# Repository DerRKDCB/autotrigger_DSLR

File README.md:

# autotrigger_DSLR
Device to automaticly take a number of long exposure pictures designed for astrophotography. 
Works with any DSLR that has a 2.5mm jack remote trigger connector and a bulb exposure mode. Here is a [Video](https://www.youtube.com/watch?v=2kZ-wBnaWUU "Video") with the device in Action

## How to use
The device uses a 2.5mm headphoe jack to simulate an remote trigger. It is powered my USB. Uses SSD1306 OLED Display as Display. With 4 buttons you can change the exposure time and the number of Pictures to take. The controller is an ESP8266 (ESP-12F module), so wifi capabilities could be implemented (**but are not, yet**).

1. Plug the USB into any USB Power source (Powerbank/Phone Charger/...) to power the device. Power consumtion is only 50mA so any Power source should work. Make sure you have a Power source that doesn't switch off because not enough current is detected.
2. Plug the headphone jack into the external/remote trigger socket of the camera.
3. Turn on the camera and change the settings to bulb mode for long exposures, if you want short exposures (under 1s) adjust exposure time at the camera accordingly.
4. Change exposure time on the autotrigger with the UP and DOWN buttons. (1s - 300s, range can be changed in code)
5. Press NEXT to select number of Exposures.
6. Change number of exposures to how much exposures you want UP and DOWN buttons. (1 - 100, range can be changed in code)
7. Press START to start the configured Series of Exposures.
8. While one Session is runnig, some info is displayed (exposure number, time of current exposure, total time)
9. Wait until session is finished or press NEXT to abort an session (current exposue will be finished)

## Building

### Ordering PCB and Parts

Order the PCB from a manufacturer you like, i use [JLCPCB](https://jlcpcb.com/ "JLCPCB"), by uploading the [prepared gerber files](KiCAD/autotrigger_dslr_v1.zip).

#### Partslist:
| Part  | Value  | Package  | Comment  | Link  |
| ------------ | ------------ | ------------ | ------------ | ------------ |
| C1  | 10uF  | 0805  |   | https://www.lcsc.com/product-detail/Multilayer-Ceramic-Capacitors-MLCC-SMD-SMT_FH-Guangdong-Fenghua-Advanced-Tech-0805X106M160NT_C2832123.html  |
| C2  | 10uF  | 0805  |   | https://www.lcsc.com/product-detail/Multilayer-Ceramic-Capacitors-MLCC-SMD-SMT_FH-Guangdong-Fenghua-Advanced-Tech-0805X106M160NT_C2832123.html  |
| C3  | 100nF  | 0805  |   | https://www.lcsc.com/product-detail/Multilayer-Ceramic-Capacitors-MLCC-SMD-SMT_FH-BK-Guangdong-Fenghua-Bangke-Elec-0805B104J500NT_C2830722.html  |
| C4  | 10uF  | 0805  |   | https://www.lcsc.com/product-detail/Multilayer-Ceramic-Capacitors-MLCC-SMD-SMT_FH-Guangdong-Fenghua-Advanced-Tech-0805X106M160NT_C2832123.html  |
| C5  | 100nF  | 0805  |   | https://www.lcsc.com/product-detail/Multilayer-Ceramic-Capacitors-MLCC-SMD-SMT_FH-BK-Guangdong-Fenghua-Bangke-Elec-0805B104J500NT_C2830722.html  |
| D1  | 1N5819  | SOD-123  |   | https://www.lcsc.com/product-detail/Schottky-Barrier-Diodes-SBD_ZHIDE-1N5819W_C2683619.html  |
| D2  | 1N5819  | SOD-123   |   | https://www.lcsc.com/product-detail/Schottky-Barrier-Diodes-SBD_ZHIDE-1N5819W_C2683619.html  |
| F1  | 500mA  | 1812  | Polyfuse  | https://www.lcsc.com/product-detail/Resettable-Fuses_TECHFUSE-mSMD050-15V_C70110.html  |
| J1  |   | 5x2.54mm  | Pin Header Female  | https://www.lcsc.com/product-detail/Female-Headers_Ckmtw-Shenzhen-Cankemeng-B-2200S05P-A120_C124414.html  |
| J2  | SSD1306  | SSD1306  | Display, look for pinout *GND VCC SCL SDA* , 4Pin, White | https://www.aliexpress.com/item/32638662748.html |
| K1  | G6K  | G6K-2F  | Omron Relay  | https://www.lcsc.com/product-detail/Signal-Relays_Omron-Electronics-G6K-2F-Y-TR-DC5_C47190.html  |
| Q1  | MosFET  | SOT-23  | N-Channel  | https://www.lcsc.com/product-detail/MOSFETs_Sinopower-Semicon-SM2326NSANC-TRG_C368561.html  |
| R1  | 10k  | 0805  |   | https://www.lcsc.com/product-detail/Chip-Resistor-Surface-Mount_TyoHM-RMC080510K1-N_C269742.html  |
| R2  | 10k  | 0805  |   | https://www.lcsc.com/product-detail/Chip-Resistor-Surface-Mount_TyoHM-RMC080510K1-N_C269742.html  |
| R3  | 1k  | 0805  |   | https://www.lcsc.com/product-detail/Chip-Resistor-Surface-Mount_TyoHM-RMC08051K5-N_C269727.html  |
| R4  | 10k  | 0805  |   | https://www.lcsc.com/product-detail/Chip-Resistor-Surface-Mount_TyoHM-RMC080510K1-N_C269742.html  |
| R5  | 5k  | 0805  |   | https://www.lcsc.com/product-detail/Chip-Resistor-Surface-Mount_Viking-Tech-ARG05DTC5001_C2828783.html  |
| R6  | 5k  | 0805  |   | https://www.lcsc.com/product-detail/Chip-Resistor-Surface-Mount_Viking-Tech-ARG05DTC5001_C2828783.html  |
| R7  | 5k  | 0805  |   | https://www.lcsc.com/product-detail/Chip-Resistor-Surface-Mount_Viking-Tech-ARG05DTC5001_C2828783.html  |
| R8  | 5k  | 0805  |   | https://www.lcsc.com/product-detail/Chip-Resistor-Surface-Mount_Viking-Tech-ARG05DTC5001_C2828783.html  |
| R9  | 1k  | 0805  |   | https://www.lcsc.com/product-detail/Chip-Resistor-Surface-Mount_TyoHM-RMC08051K5-N_C269727.html  |
| R10  | 10k  | 0805  |   | https://www.lcsc.com/product-detail/Chip-Resistor-Surface-Mount_TyoHM-RMC080510K1-N_C269742.html  |
| R11  | 1k  | 0805  |   | https://www.lcsc.com/product-detail/Chip-Resistor-Surface-Mount_TyoHM-RMC08051K5-N_C269727.html  |
| SW1  | pushbutton  | SPST SMD  |   | https://www.lcsc.com/product-detail/Tactile-Switches_XKB-Connectivity-TS-1101-C-W_C318938.html  |
| SW2  | pushbutton  | SPST SMD  |   | https://www.lcsc.com/product-detail/Tactile-Switches_XKB-Connectivity-TS-1101-C-W_C318938.html  |
| SW3  | pushbutton  | THT 6x6x10mm  |   | https://www.lcsc.com/product-detail/Tactile-Switches_G-Switch-GT-TC096A-H100-L1_C963363.html  |
| SW4  | pushbutton  | THT 6mm_H9.5mm  |   | https://www.lcsc.com/product-detail/Tactile-Switches_G-Switch-GT-TC096A-H100-L1_C963363.html  |
| SW5  | pushbutton  | THT 6mm_H9.5mm  |   | https://www.lcsc.com/product-detail/Tactile-Switches_G-Switch-GT-TC096A-H100-L1_C963363.html  |
| SW6  | pushbutton  | THT 6mm_H9.5mm  |   | https://www.lcsc.com/product-detail/Tactile-Switches_G-Switch-GT-TC096A-H100-L1_C963363.html  |
| U1  | ESP8266  | ESP-12F  |   | https://www.lcsc.com/product-detail/WiFi-Modules_Ai-Thinker-ESP-12F-ESP8266MOD_C82891.html  |
| U2  | AMS1117-3.3  | SOT-223-3  |   | https://www.lcsc.com/product-detail/Linear-Voltage-Regulators-LDO_PUOLOP-AMS1117-3-3_C351784.html  |

#### You also need:
- 1x USB A cable (any can be used because it's solderd directly to the pcb)
- 1x 2.5mm headphone jack cable https://www.aliexpress.com/item/4001182848617.html
- 8x M2.5 5mm bolts https://www.aliexpress.com/item/32963722509.html
- cable ties for strain relief
- tape (electrical/kepton/... doesn't really matter)
- For programming: USB to serial Adapter and jumper cables

### 3D Printing
Print [case](FreeCAD/3dp/stl/case-case.stl) and [lid](FreeCAD/3dp/stl/case-led.stl) in PLA (recommended, but doesn't really matter) and standard settings.

### Soldering

1. Start soldering all SMD components, using the [schematic](doc/autotrigger_DSLR_v1_schematic.pdf) and the partslist above. Diode cathodes are indicated with "-".
2. Solder Programming Pin headers and THT pushbuttons.
3. Isolate the backside of the SSD1306 OLED Display with some tape, then solder in place.
4. Before soldering wires put them though holes in the case.
5. USB A cable: strip wire and check which is +5V (propably red) and GND (propably black) using a multimeter. Then solder to J4.
6. Headphone Jack cable: cut away female jack. Strip wire and tin the tips so that the isolating coating is burnt way (thats the way i do it). Then check which are the needed wires (multimeter continuity) and solder to J3, according to picture below.

### Assembly

1. Screw PCB to case using four M2.5 bolts.
2. Put a zip tie around both cables to wirk as strain relief.
3. Now upload software to the autotrigger, see *Configuration and Programming* section.
4. Screw lid to case using four M2.5 bolts.

## Configuration and Programming

1. autotrigger_DSLR is programmed in the [PlatformIO IDE](https://docs.platformio.org/en/latest/integration/ide/vscode.html#ide-vscode "PlatformIO IDE"). PlatformIO is needed to upload the Software to the autotrigger.
2. Open Project in PlatformIO
3. Open [src/main.cpp](src/main.cpp)
4. Change function options at the top of the document, if needed (more explosures, longer exposures, ...)
```cpp
//Function Options
#define minExposure 1000 //minimum exposure time in ms
#define maxExposure 300000 //maximum exposure time in ms
#define minNumberOfExposures 1
#define maxNumberOfExposures 100 //absolute max 255
#define waitingTimeBetweenExposures 2000 //time the controller waits for camera until it starts the next exposure
```
5. If buttons don't work properly, you may have to increase `buttonTolerance` or adjust button values
```cpp
//Button Values
#define valueButtonUp 588
#define valueButtonDown 328
#define valueButtonNext 231
#define valueButtonStart 181
#define buttonTolerance 10
```
6. Connect the autotrigger via USB to Serial Adapter. Only connect 5V **OR** 3.3V

| Serial Adapter  | autotrigger  |
| ------------ | ------------ |
| GND  | GND  |
| 5V  | 5  |
| **or** 3.3V  | **or** 3.3  |
| TX  | RX  |
| RX  | TX  |

7. Hit Upload, press both boot and reset button, release reset button, wait till upload has started, release boot button.
8. Wait until upload is finished.
9. press reset.
10. **ENJOY**

## Todo
- Mounting holes PCB need adjusdment, false measurement

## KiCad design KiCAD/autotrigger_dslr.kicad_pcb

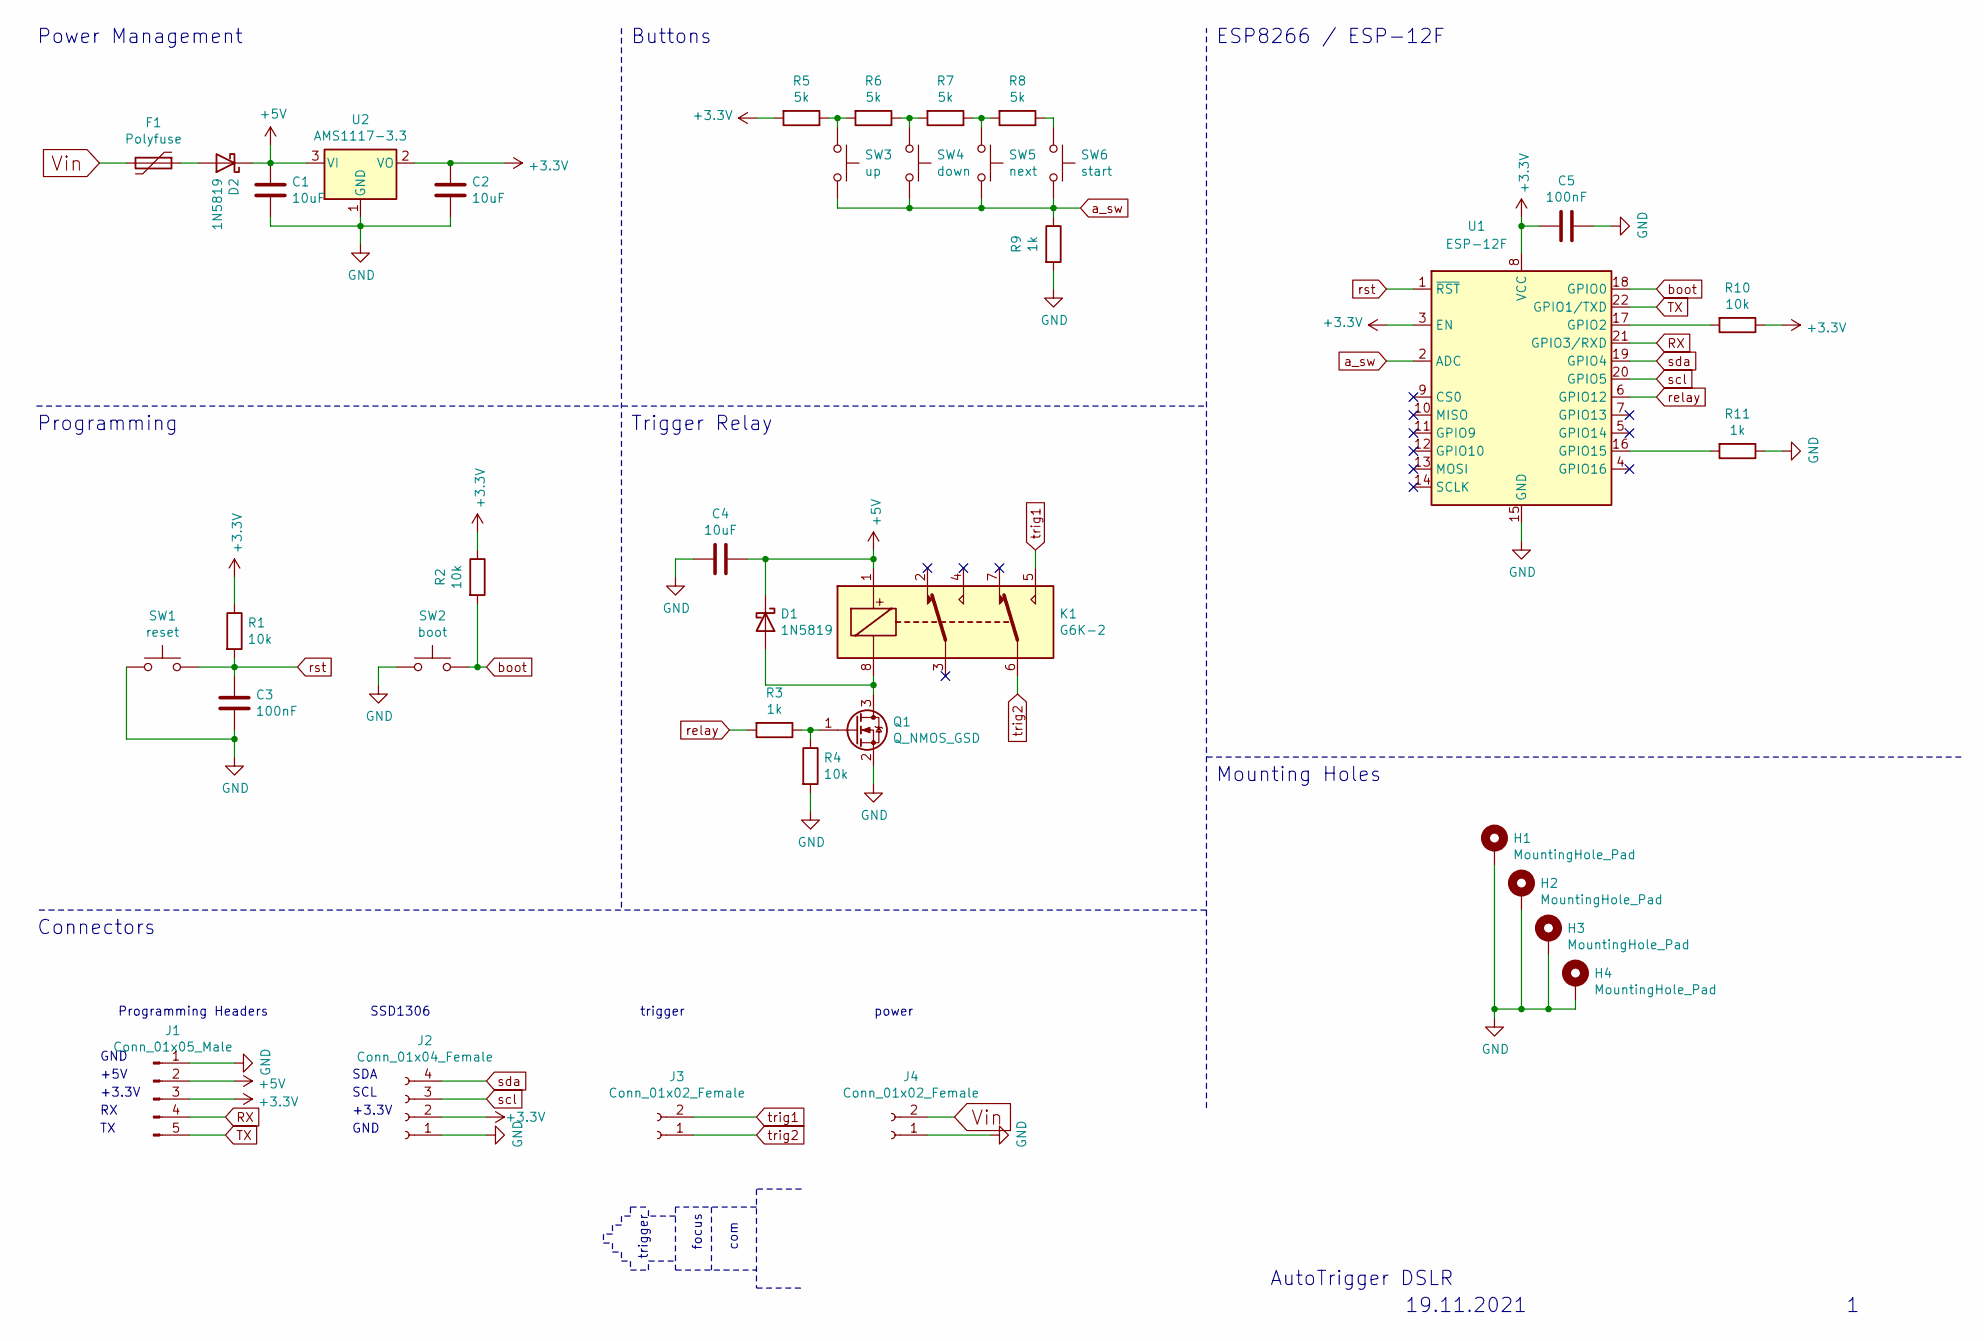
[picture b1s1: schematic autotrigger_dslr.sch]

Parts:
C1, C2, C4: 10uF; C_0805_2012Metric_Pad1.18x1.45mm_HandSolder
C3, C5: 100nF; C_0805_2012Metric_Pad1.18x1.45mm_HandSolder
D1, D2: 1N5819; D_SOD-123
F1: Polyfuse; Fuse_1812_4532Metric_Pad1.30x3.40mm_HandSolder
H1, H2, H3, H4: MountingHole_Pad; MountingHole_2.7mm_M2.5_Pad
J1: Conn_01x05_Male; PinHeader_1x05_P2.54mm_Vertical
J2: Conn_01x04_Female; PinHeader_1x04_P2.54mm_Vertical
J3, J4: Conn_01x02_Female; PinHeader_1x02_P2.54mm_Vertical
K1: G6K-2; Relay_DPDT_Omron_G6K-2F-Y
Q1: Q_NMOS_GSD; SOT-23_Handsoldering
R1, R2, R4, R10: 10k; R_0805_2012Metric_Pad1.20x1.40mm_HandSolder
R3, R9, R11: 1k; R_0805_2012Metric_Pad1.20x1.40mm_HandSolder
R5, R6, R7, R8: 5k; R_0805_2012Metric_Pad1.20x1.40mm_HandSolder
SW1: reset; SW_SPST_FSMSM
SW2: boot; SW_SPST_FSMSM
SW3: up; SW_PUSH_6mm_H9.5mm
SW4: down; SW_PUSH_6mm_H9.5mm
SW5: next; SW_PUSH_6mm_H9.5mm
SW6: start; SW_PUSH_6mm_H9.5mm
U1: ESP-12F; ESP-12E
U2: AMS1117-3.3; SOT-223-3_TabPin2

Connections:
+3V3: C2.1, C5.2, J1.3, J2.2, R1.1, R2.1, R5.2, R10.1, U1.3 (EN), U1.8 (VCC), U2.2 (VO)
+5V: C1.1, C4.1, D1.1 (K), D2.1 (K), J1.2, K1.1, U2.3 (VI)
GND: C1.2, C2.2, C3.2, C4.2, C5.1, H1.1, H2.1, H3.1, H4.1, J1.1, J2.1, J4.1, Q1.2 (S), R4.2, R9.2, R11.1, SW1.1, SW2.1, U1.15 (GND), U2.1 (GND)
unnamed: D1.2 (A), K1.8, Q1.3 (D)
unnamed: D2.2 (A), F1.1
unnamed: Q1.1 (G), R3.1, R4.1
unnamed: R5.1, R6.2, SW3.1
unnamed: R6.1, R7.2, SW4.1
unnamed: R7.1, R8.2, SW5.1
unnamed: R8.1, SW6.1
unnamed: R10.2, U1.17 (GPIO2)
unnamed: R11.2, U1.16 (GPIO15)
RX: J1.4, U1.21 (GPIO3/RXD)
TX: J1.5, U1.22 (GPIO1/TXD)
Vin: F1.2, J4.2
a_sw: R9.1, SW3.2, SW4.2, SW5.2, SW6.2, U1.2 (ADC)
boot: R2.2, SW2.2, U1.18 (GPIO0)
relay: R3.2, U1.6 (GPIO12)
rst: C3.1, R1.2, SW1.2, U1.1 (~RST)
scl: J2.3, U1.20 (GPIO5)
sda: J2.4, U1.19 (GPIO4)
trig1: J3.2, K1.5
trig2: J3.1, K1.6

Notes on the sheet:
GND
+5V
+3.3V
SCL
SDA
Programming Headers
SSD1306
trigger
com
focus
power
Connectors
Programming
Trigger Relay
Buttons
Power Management
ESP8266 / ESP-12F
19.11.2021
AutoTrigger DSLR
Mounting Holes

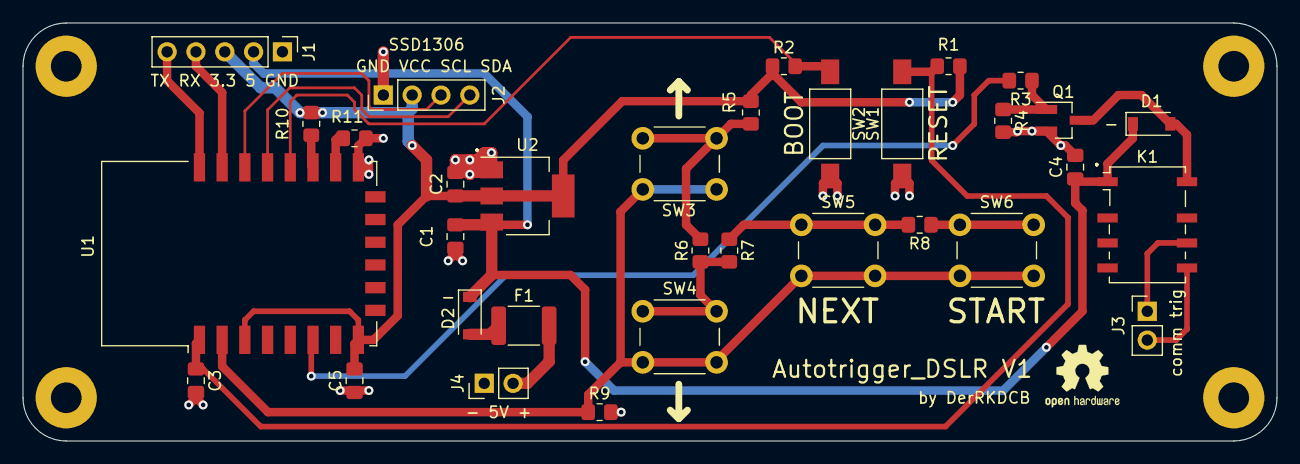
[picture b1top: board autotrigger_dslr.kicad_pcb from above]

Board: 2 copper layers, 110.5 x 36.8 mm, 38 parts (1 on the bottom side), 23 nets.

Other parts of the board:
QR*****: DerRKDCB; Rickroll

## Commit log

2021-12-30 add freecad case file
2021-12-30 added kicad files
2021-12-30 add pcb step to freecad
2021-12-30 ignore FCStd1 files
2021-12-30 designed case
2021-12-31 stl and slicing
2021-12-31 change exposure time
2022-01-01 rename folder
2022-01-05 implemented settings screen
2022-01-05 implemented session and session screen
2022-01-06 change variable types
2022-01-06 changed time waited between pictures to 2s
2022-01-06 remove gcode files
2022-01-06 removed FCStd1 file
2022-01-06 show current exposure time
2022-01-06 abort function
2022-01-15 regenerated gerber files
2022-01-15 add How to use and Partslist
2022-01-15 add soldering and assembly
2022-01-15 comments at configuration
2022-01-15 add programming and links
2022-01-15 link gerber files
2022-01-15 doc img and schematic
2022-01-15 add pictures and links
2022-02-01 screw holes PCB trough hole
2022-02-01 remove todo screwholes
